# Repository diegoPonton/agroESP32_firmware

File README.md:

<h1 align="center">AgroESP32</h1>

<p align="center">
  <b>Red de sensores agrícolas de largo alcance:</b> nodos LoRa 915 MHz sobre una PCB de diseño propio,<br>
  un gateway WiFi y una plataforma web en la nube para monitorear y actuar sobre un cultivo a distancia.
</p>

<p align="center">

</p>

<p align="center">
  
  <br>
  <sub>Prototipo armado: PCB propia con el XIAO ESP32-S3 y el RFM95W, antena de 915 MHz y carcasa impresa en 3D</sub>
</p>

> **Hardware diseñado por mí.** La PCB del nodo (esquemático, ruteo, Gerbers y BOM) la diseñé en KiCad 10: un carrier de 75 × 51 mm para el Seeed XIAO ESP32-S3 y un módulo LoRa RFM95W, con borneras para conectar sensores y actuadores en campo sin soldar. Los archivos fuente están en [`hardware/`](hardware/).

---

## Contenido

- [El problema](#el-problema)
- [Resultados](#resultados)
- [Arquitectura](#arquitectura)
- [Hardware](#hardware)
  - [PCB del nodo XIAO (diseño propio)](#pcb-del-nodo-xiao-diseño-propio)
  - [Esquemático y mapa de conexiones](#esquemático-y-mapa-de-conexiones)
  - [BOM](#bom)
  - [Del diseño al nodo en campo](#del-diseño-al-nodo-en-campo)
  - [Nodo ESP32 DOIT y gateway](#nodo-esp32-doit-y-gateway)
- [Firmware](#firmware)
- [Plataforma web](#plataforma-web)
- [Pruebas de alcance](#pruebas-de-alcance)
- [Problemas de ingeniería resueltos](#problemas-de-ingeniería-resueltos)
- [Qué demuestra este proyecto](#qué-demuestra-este-proyecto)
- [Estructura del repositorio](#estructura-del-repositorio)
- [Compilar y flashear](#compilar-y-flashear)
- [Próximos pasos](#próximos-pasos)

---

## El problema

Monitorear un cultivo normalmente obliga a ir hasta el terreno. Las zonas rurales suelen no tener WiFi, cobertura celular ni tomas de corriente cerca, y las soluciones IoT comerciales son caras y dependen de suscripciones.

AgroESP32 resuelve eso con radio **LoRa a 915 MHz** (banda ISM, sin licencia): nodos de bajo consumo miden el ambiente en el cultivo y transmiten a un gateway que sí tiene internet. Desde un panel web se ven los datos en tiempo real y se mandan órdenes de vuelta a los nodos, incluida la activación de una **bomba de agua** a través de un relé de estado sólido.

## Resultados

| | |
|---|---|
| **594,66 m** | enlace más largo con recepción confirmada, sin línea de vista (edificios densos y bosque) |
| **−38 a −100 dBm** | rango de RSSI registrado en la plataforma |
| **500 lecturas** | recibidas en prueba continua con intervalo de 1 min |
| **3 tipos de nodo** | emisor XIAO (PCB propia), emisor ESP32 DOIT multi-sensor y gateway |
| **75 × 51 mm** | PCB de 2 capas, solo componentes THT, sin vías |
| **Lazo cerrado** | la plataforma no solo lee: enciende y apaga una bomba vía `set_relay` |

## Arquitectura

```mermaid
flowchart LR
    subgraph Campo["En el cultivo"]
        XIAO["Nodo XIAO ESP32-S3<br/>PCB propia<br/>BME280 + relé SSR"]
        DOIT["Nodo ESP32 DOIT<br/>SHTC3 · DS18B20 · GPS · batería"]
        Bomba["Bomba de agua"]
        XIAO -->|SSR en D0| Bomba
    end

    GW["Gateway ESP32 DOIT<br/>RFM95W + WiFi"]

    subgraph Nube["Railway"]
        API["Django REST<br/>+ Channels"]
        PG[("PostgreSQL")]
        RD[("Redis")]
        WEB["Next.js<br/>panel en tiempo real"]
    end

    XIAO <-->|LoRa 915 MHz| GW
    DOIT <-->|LoRa 915 MHz| GW
    GW -->|"HTTPS: POST telemetría<br/>GET relay de comandos"| API
    API --> PG
    API --> RD
    API <-->|REST + WebSocket| WEB
```

La telemetría sube como JSON por LoRa. El gateway le agrega el RSSI real del paquete y la publica en la API. Los comandos hacen el camino inverso: el gateway consulta si hay órdenes pendientes para ese nodo y las retransmite durante una ventana de escucha que el nodo abre después de cada transmisión. El gateway no necesita saber qué hardware tiene cada nodo; enruta todo por `device_id`.

<details>
<summary><b>Diagramas del documento de diseño</b></summary>
<br>

**Diagrama de contexto**

**Diagrama de bloques**

Ambos corresponden a la fase de diseño, con el nodo ESP32 DOIT como emisor de referencia. El documento completo está en [`docs/DISENO.md`](docs/DISENO.md).

</details>

---

## Hardware

### PCB del nodo XIAO (diseño propio)

<table>
  <tr>
    <td width="50%"></td>
    <td width="50%"></td>
  </tr>
  <tr>
    <td align="center"><sub>Layout en KiCad: F.Cu (rojo) y B.Cu (azul), plano de GND en ambas caras</sub></td>
    <td align="center"><sub>Vista 3D superior con los módulos montados</sub></td>
  </tr>
  <tr>
    <td width="50%"></td>
    <td width="50%"></td>
  </tr>
  <tr>
    <td align="center"><sub>Render isométrico</sub></td>
    <td align="center"><sub>Cara inferior (B.Cu)</sub></td>
  </tr>
</table>

**Especificaciones**

| Parámetro | Valor |
|---|---|
| Herramienta | KiCad 10 (esquemático + PCB + render 3D) |
| Dimensiones | 75 × 51 mm |
| Capas | 2 (F.Cu / B.Cu), FR-4 de 1,6 mm |
| Ancho de pista | 0,2 mm en todas las señales |
| Planos de cobre | GND en ambas caras |
| Vías | 0: todo el ruteo se resolvió en dos capas sin vías |
| Montaje | 100 % THT, soldable a mano sin equipo de SMD |
| Fijación | 4 agujeros de montaje en las esquinas |
| Conectores de campo | borneras de tornillo de 5,00 mm (MaiXu MX126) |

**Decisiones de diseño**

- **Módulos enchufables en vez de chips sueltos.** El XIAO ESP32-S3 y el breakout del RFM95W van montados como módulos. Si uno falla en campo se reemplaza sin desoldar, y la placa queda simple de fabricar y ensamblar.
- **Un puerto por bus.** Cada bornera expone una interfaz completa con su propio 3,3 V y GND, así cualquier sensor se conecta con un destornillador:
  - **J1:** entrada de alimentación (3,3 V / GND)
  - **J2:** I2C (3,3 V, GND, SDA, SCL), hoy el BME280
  - **J3:** UART (3,3 V, GND, TX, RX), reservado para un GPS
  - **J4:** GPIO/ADC (3,3 V, GND, D0), hoy maneja el relé SSR; como D0 es el único pin libre con ADC, también sirve para medir batería
- **SPI por hardware.** El RFM95W usa los pines SPI nativos del XIAO (D8, D9, D10), y CS, RST y DIO0 van a GPIO de propósito general.
- **Radio siempre habilitada.** El pin `EN` del breakout está atado a 3,3 V, y el pin de 5 V del XIAO queda sin conectar a propósito para que toda la placa trabaje en un único riel de 3,3 V.
- **Pistas cortas al módulo de radio.** El RFM95W queda al lado del XIAO para acortar las líneas SPI, con planos de GND como referencia de retorno.

### Esquemático y mapa de conexiones

También en PDF: [`hardware/esquematico.pdf`](hardware/esquematico.pdf).

Mapa de conexiones, extraído de la netlist del esquemático:

| Pin XIAO | GPIO | Red | Destino |
|---|---|---|---|
| D0 | GPIO1 | `adc` | J4-3 (GPIO/ADC → relé SSR) |
| D1 | GPIO2 | `LORA_DIO0` | U2 G0 |
| D2 | GPIO3 | `LORA_RST` | U2 RST |
| D3 | GPIO4 | `LORA_CS` | U2 CS |
| D4 | GPIO5 | `sda` | J2-3 |
| D5 | GPIO6 | `scl` | J2-4 |
| D6 | GPIO43 | `TX` | J3-3 |
| D7 | GPIO44 | `RX` | J3-4 |
| D8 | GPIO7 | `LORA_SCK` | U2 SCK |
| D9 | GPIO8 | `LORA_MISO` | U2 MISO |
| D10 | GPIO9 | `LORA_MOSI` | U2 MOSI |
| 3V3 | — | `+3.3V` | J1–J4 pin 1, U2 VIN, U2 EN |
| GND | — | `GND` | J1–J4 pin 2, U2 GND |
| 5V | — | sin conectar | — |

> En la PCB, `DIO0` y `RST` del RFM95W quedaron en D1 y D2 respectivamente, al revés que en el primer prototipo en protoboard (RST en D1, DIO0 en D2). Hay que tenerlo en cuenta al configurar `LORA_RST_PIN` y `LORA_DIO0_PIN` en `src/emisor_xiao/board_config.h`.

### BOM

**Componentes de la PCB** (exportado de KiCad: [`hardware/BOM.csv`](hardware/BOM.csv))

| Ref | Cant. | Componente | Función | Huella |
|---|---|---|---|---|
| U1 | 1 | Seeed Studio XIAO ESP32-S3 Plus | MCU: ESP32-S3, WiFi + BLE, USB-C, carga de LiPo integrada | `XIAO_ESP32_S3:MODULE_XIAO_ESP32_S3` |
| U2 | 1 | Adafruit RFM95W LoRa breakout, 915 MHz | Transceptor LoRa (SX1276) por SPI | `3073:MODULE_3073` |
| J1 | 1 | Bornera 2 pines, paso 5,00 mm (MaiXu MX126-5.0-02P) | Entrada de alimentación 3,3 V | `TerminalBlock_MaiXu_MX126-5.0-02P_1x02_P5.00mm` |
| J2, J3 | 2 | Bornera 4 pines, paso 5,00 mm (MaiXu MX126-5.0-04P) | Puertos I2C y UART | `TerminalBlock_MaiXu_MX126-5.0-04P_1x04_P5.00mm` |
| J4 | 1 | Bornera 3 pines, paso 5,00 mm (MaiXu MX126-5.0-03P) | Puerto GPIO/ADC | `TerminalBlock_MaiXu_MX126-5.0-03P_1x03_P5.00mm` |
| — | 1 | PCB 75 × 51 mm, 2 capas, FR-4 1,6 mm | Placa base | [`hardware/fabricacion/`](hardware/fabricacion/) |

> La huella de U2 es la de Adafruit 3073 (RFM96W, 433 MHz), que comparte contorno y pinout con la versión de 915 MHz (Adafruit 3072). En la placa va montada la de **915 MHz**.

**Componentes externos del nodo** (conectados por bornera o al XIAO)

| Componente | Cant. | Conexión | Función |
|---|---|---|---|
| BME280 breakout (I2C, 0x76/0x77) | 1 | J2 | Temperatura, humedad y presión atmosférica |
| Módulo relé de estado sólido (SSR) | 1 | J4 (D0) | Encendido de la bomba de agua |
| Bomba de agua | 1 | Salida del SSR | Actuador de riego |
| Antena 915 MHz con conector SMA (DIYmall) | 1 | Breakout RFM95W | Enlace LoRa |
| Antena 2,4 GHz u.FL (incluida con el XIAO) | 1 | XIAO ESP32-S3 | WiFi / BLE |
| Batería LiPo 3,7 V, 1 celda | 1 | Conector `BAT` del XIAO | Alimentación autónoma, se carga por USB-C |
| Carcasa impresa en 3D | 1 | — | Encapsulado del nodo para campo |

### Del diseño al nodo en campo

El proceso: selección de componentes, diseño de la placa en KiCad, montaje y cableado del circuito, y encapsulado de los nodos para llevarlos al campo.

### Nodo ESP32 DOIT y gateway

Además del nodo XIAO, el sistema tiene dos equipos sobre **ESP32 DOIT DevKit V1**:

**Nodo emisor multi-sensor**

| Señal | GPIO |
|---|---|
| RFM95W: CS / RST / DIO0 | 25 / 14 / 26 |
| RFM95W: SCK / MISO / MOSI | 18 / 19 / 23 |
| SHTC3 (I2C): SDA / SCL | 21 / 22 |
| DS18B20 (OneWire, pull-up 4,7 kΩ) | 4 |
| GPS (UART): RX / TX | 16 / 17 |
| Batería (ADC, divisor 1:1) | 34 |

**Gateway receptor:** mismo módulo RFM95W y mismos pines de radio, en recepción continua por interrupción. Usa el WiFi del ESP32 para publicar en la nube y transmite a 13 dBm (los emisores, a 20 dBm).

**Perfil de radio común**

| Parámetro | Valor |
|---|---|
| Frecuencia | 915,0 MHz (ISM) |
| Spreading factor / ancho de banda | SF7 / 125 kHz |
| Coding rate | 4/5 |
| Sync word | `0x12` (red privada) |
| Payload máximo | 250 bytes |

---

## Firmware

Un solo proyecto **PlatformIO** (C++ / Arduino) con un entorno por equipo:

| Entorno | Placa | Rol |
|---|---|---|
| `emisor` | ESP32 DOIT DevKit V1 | Nodo multi-sensor: SHTC3, DS18B20, GPS, batería |
| `emisor_xiao` | Seeed XIAO ESP32-S3 | Nodo de la PCB: BME280 + relé SSR |
| `receptor` | ESP32 DOIT DevKit V1 | Gateway LoRa → WiFi → API |

**Características**

- **RadioLib** sobre el SX1276. TX y RX bloqueantes leyendo el pin de IRQ, sin acceso SPI dentro de interrupciones (ver [problemas resueltos](#problemas-de-ingeniería-resueltos)).
- **Configuración en tres niveles:** NVS (`Preferences`) → `secrets.h` generado por la plataforma → modo *provisioning* que espera un JSON por serial. Las credenciales nunca se versionan.
- **Payload JSON adaptativo:** si el paquete supera 250 bytes, el nodo DOIT recorta el bloque GPS por niveles (todo → sin altitud/velocidad/HDOP → solo lat/lon → sin GPS).
- **Comandos remotos** recibidos en una ventana de escucha de 7 s después de cada TX y persistidos en NVS:

| Comando | Parámetros | Efecto |
|---|---|---|
| `set_sleep` | `{"minutes": N}` | Cambia el intervalo de envío (1–1440 min) |
| `enable_sensor` | `{"sensor": "...", "enable": bool}` | Activa o desactiva un sensor (nodo DOIT) |
| `set_relay` | `{"state": bool}` | Enciende o apaga el relé SSR (nodo XIAO); el estado sobrevive a reinicios |
| `set_device_id` | `{"device_id": "..."}` | Reasigna el ID y reinicia |
| `restart` | `{}` | Reinicio por software |

**Ejemplo de payload del nodo XIAO**

```json
{
  "device_id": "e2",
  "amb": { "ok": true, "temp_c": 24.8, "hum_pct": 52.3, "pressure_hpa": 1013.2 },
  "relay": { "on": false },
  "rssi": -38
}
```

`rssi` lo agrega el gateway con la medición real del paquete recibido.

**Ciclo de vida del nodo (diseño)**

El diseño contempla *deep sleep* entre ciclos con caché del GPS en memoria RTC (arranque en caliente ≤ 30 s contra 60 s en frío). Los builds de prueba transmiten cada ~10 s para iterar rápido sobre el enlace.

---

## Plataforma web

Código en el repositorio [**AgroPlatfrom**](https://github.com/diegoPonton/AgroPlatfrom), desplegado en Railway con auto-deploy desde `main`.

| Capa | Tecnología |
|---|---|
| Backend | Django 5, Django REST Framework, Django Channels (WebSocket) |
| Datos | PostgreSQL, Redis como channel layer |
| Frontend | Next.js (App Router), TanStack Query, Recharts, Leaflet, shadcn/ui |
| Infraestructura | Railway: 4 servicios, migraciones automáticas en cada deploy |

**Funcionalidades**

- Autenticación JWT y organizaciones multi-usuario.
- Registro de nodos y asignación de cada emisor a su gateway.
- Ingesta de telemetría autenticada con el token del gateway; cada lectura guarda qué gateway la recibió.
- Panel en tiempo real por WebSocket: KPIs, historial graficado, RSSI y mapa GPS.
- Cola de comandos con estados (`pending` → `relayed` → `acked`) retransmitidos por el gateway.
- Generación de `secrets.h` por dispositivo y **flasheo de firmware desde el navegador** (Web Serial + esptool-js).

---

## Pruebas de alcance

El enlace se probó en un campus universitario con edificios densos, arbolado y un lago, **sin línea de vista despejada** en ninguno de los tres trayectos:

| Prueba | Trayecto | Distancia | Resultado |
|---|---|---|---|
| 1 | Entre bloques de aulas | 295,00 m | Recepción confirmada |
| 2 | Sobre bosque y lago | **594,66 m** | Recepción confirmada (enlace más largo) |
| 3 | Patio y arbolado interior | 201,57 m | Recepción confirmada |

Durante las pruebas la plataforma registró 500 lecturas con intervalo de 1 minuto y RSSI entre −38 y −100 dBm. Con línea de vista, LoRa a SF7 alcanza bastante más; estas cifras son el peor caso urbano.

---

## Problemas de ingeniería resueltos

Una parte importante del proyecto fue depurar hardware real:

- **Sensor mal identificado.** Una placa vendida como "GY-39" se trató primero como BME280 y nunca respondió. Al revisar el hardware resultó ser un módulo 4 en 1 con un **SPL06-007** para presión, cuyos registros no coinciden con los del BME280. La solución fue leer directamente el **SHTC3** que la misma placa expone en I2C (`0x70`), y usar un BME280 genuino en el nodo XIAO.
- **TX colgado con RadioHead.** Después de esperar ~60 s el fix del GPS, el SX1276 no volvía a STANDBY y cada transmisión daba timeout (`IRQ_FLAGS = 0x00`, nunca `TxDone`). Además, acceder a SPI dentro de la ISR de DIO0 provocaba reinicios. Migrar a **RadioLib** con TX/RX bloqueantes por sondeo del pin IRQ eliminó ambos problemas.
- **Pines intercambiados entre prototipo y PCB.** En la placa propia, RST y DIO0 del RFM95W quedaron en pines distintos a los del prototipo en protoboard, así que la asignación de pines del prototipo no servía para la placa. Se corrigió reasignando los pines en el firmware, sin rehacer la PCB.
- **404 en la ingesta.** Al sumar un nodo nuevo, la API devolvía 404. No era un bug: el backend solo acepta telemetría de dispositivos registrados en la misma organización que el gateway, una restricción de seguridad multi-tenant intencional.

## Qué demuestra este proyecto

| Área | Habilidades |
|---|---|
| **Diseño de hardware** | Captura de esquemático, ruteo de PCB de 2 capas, planos de GND, generación de Gerbers y BOM en KiCad; selección de componentes; montaje y depuración con multímetro |
| **Sistemas embebidos** | ESP32 / ESP32-S3, buses SPI, I2C, UART, OneWire y ADC; NVS; manejo de interrupciones; gestión de energía |
| **Radiofrecuencia** | Configuración de LoRa (SF, BW, CR, sync word), pruebas de alcance en campo, análisis de RSSI |
| **Firmware** | C++ / Arduino con PlatformIO, protocolo propio sobre LoRa, comandos remotos con persistencia, aprovisionamiento seguro de credenciales |
| **Backend y cloud** | Django REST, WebSocket con Channels, PostgreSQL, Redis, despliegue continuo en Railway |
| **Frontend** | Next.js, visualización en tiempo real, Web Serial API para flashear dispositivos desde el navegador |

---

## Estructura del repositorio

```
agroESP32_firmware/
├── hardware/
│   ├── kicad/                  # Proyecto KiCad 10 (esquemático + PCB)
│   ├── fabricacion/            # Gerbers + taladros listos para enviar a fabricar
│   ├── BOM.csv                 # Lista de materiales exportada de KiCad
│   └── esquematico.pdf
├── src/
│   ├── emisor/                 # Nodo ESP32 DOIT multi-sensor
│   ├── emisor_xiao/            # Nodo XIAO ESP32-S3 (PCB propia)
│   └── receptor/               # Gateway LoRa → WiFi
├── docs/
│   ├── DISENO.md               # Documento de diseño (alcance, diagramas, plan de pruebas, referencias)
│   ├── RESUMEN_TECNICO.md      # Estado técnico detallado y bitácora de decisiones
│   └── images/
└── platformio.ini
```

Los modelos 3D STEP del XIAO y del breakout de Adafruit son de terceros y no se incluyen. Para el render 3D en KiCad, descargalos de Seeed Studio y Adafruit y colocalos en `hardware/kicad/3dModels/`.

## Compilar y flashear

Requiere [PlatformIO](https://platformio.org/).

```bash
git clone https://github.com/diegoPonton/agroESP32_firmware.git
cd agroESP32_firmware

# Cada equipo necesita su secrets.h (no versionado)
cp src/emisor_xiao/secrets.h.example src/emisor_xiao/secrets.h

pio run -e emisor_xiao -t upload --upload-port COMx
pio device monitor -e emisor_xiao -p COMx
```

Lo mismo aplica para `emisor` y `receptor`. Sin `secrets.h`, el equipo arranca en modo provisioning y espera su configuración por serial.

Para fabricar la placa, subí [`hardware/fabricacion/agroESP32_PCB_gerbers.zip`](hardware/fabricacion/agroESP32_PCB_gerbers.zip) a cualquier fabricante de PCB (2 capas, 1,6 mm).

## Próximos pasos

- **Riego automático:** usar las lecturas de temperatura y humedad (déficit de presión de vapor) para decidir cuándo encender la bomba con `set_relay`, cerrando el lazo sin intervención humana.
- *Deep sleep* en los builds de campo para llevar la autonomía a meses.
- Cifrado AES del enlace LoRa.
- Medición de batería en el nodo XIAO por D0 (ADC) con divisor resistivo.
- Carcasa sellada para intemperie.
- Flasheo del nodo XIAO desde la plataforma web.

---

## Autor

**Diego Pontón Vaca**: diseño de PCB, firmware y plataforma web.

Documentación completa del diseño: [`docs/DISENO.md`](docs/DISENO.md) · Estado técnico detallado: [`docs/RESUMEN_TECNICO.md`](docs/RESUMEN_TECNICO.md)

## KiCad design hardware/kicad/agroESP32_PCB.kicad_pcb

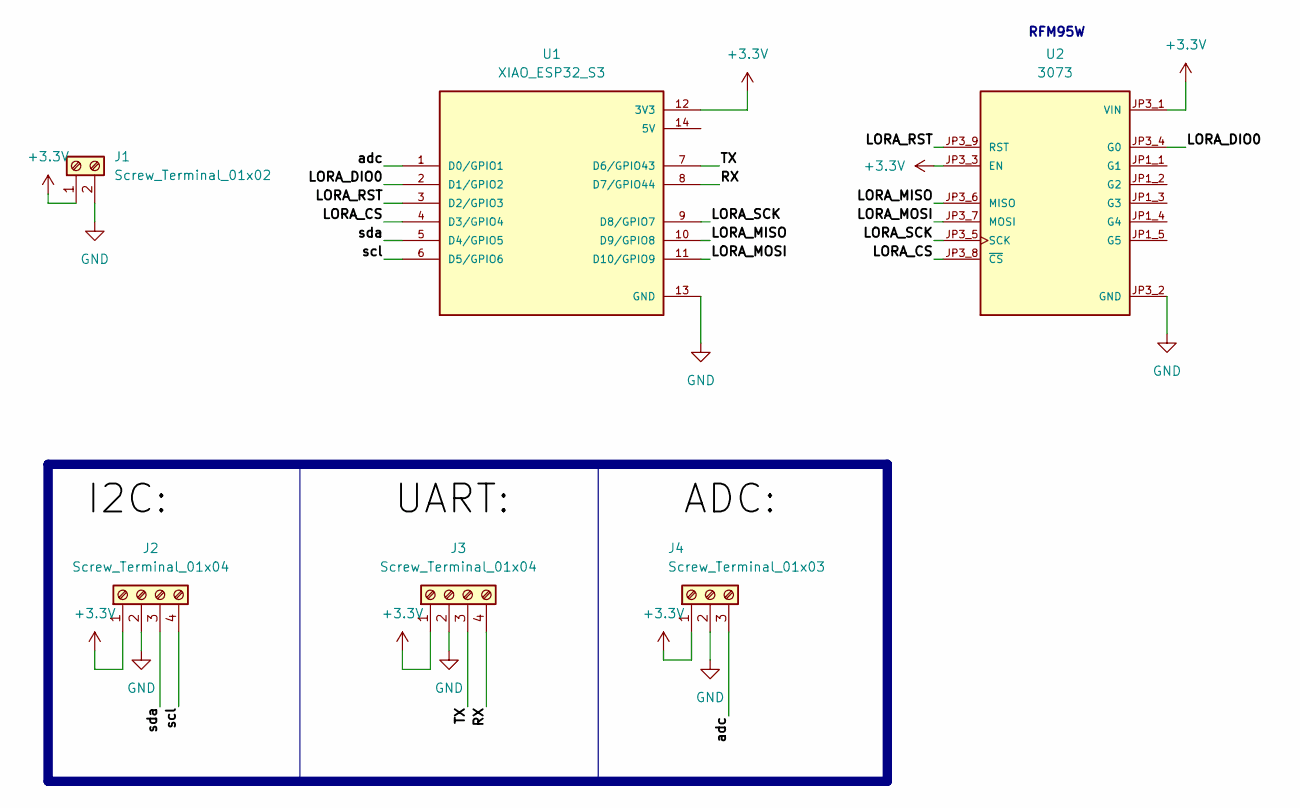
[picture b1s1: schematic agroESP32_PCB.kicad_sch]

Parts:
J1: Screw_Terminal_01x02; TerminalBlock_MaiXu_MX126-5.0-02P_1x02_P5.00mm
J2, J3: Screw_Terminal_01x04; TerminalBlock_MaiXu_MX126-5.0-04P_1x04_P5.00mm
J4: Screw_Terminal_01x03; TerminalBlock_MaiXu_MX126-5.0-03P_1x03_P5.00mm
U1: XIAO_ESP32_S3; MODULE_XIAO_ESP32_S3; PARTREV April 22nd, 2026
U2: 3073; MODULE_3073; PARTREV 2023-10-24

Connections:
+3.3V: J1.1, J2.1, J3.1, J4.1, U1.12 (3V3), U2.JP3_1 (VIN), U2.JP3_3 (EN)
/LORA_CS: U1.4 (D3/GPIO4), U2.JP3_8 (~CS)
/LORA_DIO0: U1.2 (D1/GPIO2), U2.JP3_4 (G0)
/LORA_MISO: U1.10 (D9/GPIO8), U2.JP3_6 (MISO)
/LORA_MOSI: U1.11 (D10/GPIO9), U2.JP3_7 (MOSI)
/LORA_RST: U1.3 (D2/GPIO3), U2.JP3_9 (RST)
/LORA_SCK: U1.9 (D8/GPIO7), U2.JP3_5 (SCK)
/RX: J3.4, U1.8 (D7/GPIO44)
/TX: J3.3, U1.7 (D6/GPIO43)
/adc: J4.3, U1.1 (D0/GPIO1)
/scl: J2.4, U1.6 (D5/GPIO6)
/sda: J2.3, U1.5 (D4/GPIO5)
GND: J1.2, J2.2, J3.2, J4.2, U1.13 (GND), U2.JP3_2 (GND)

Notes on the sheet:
RFM95W

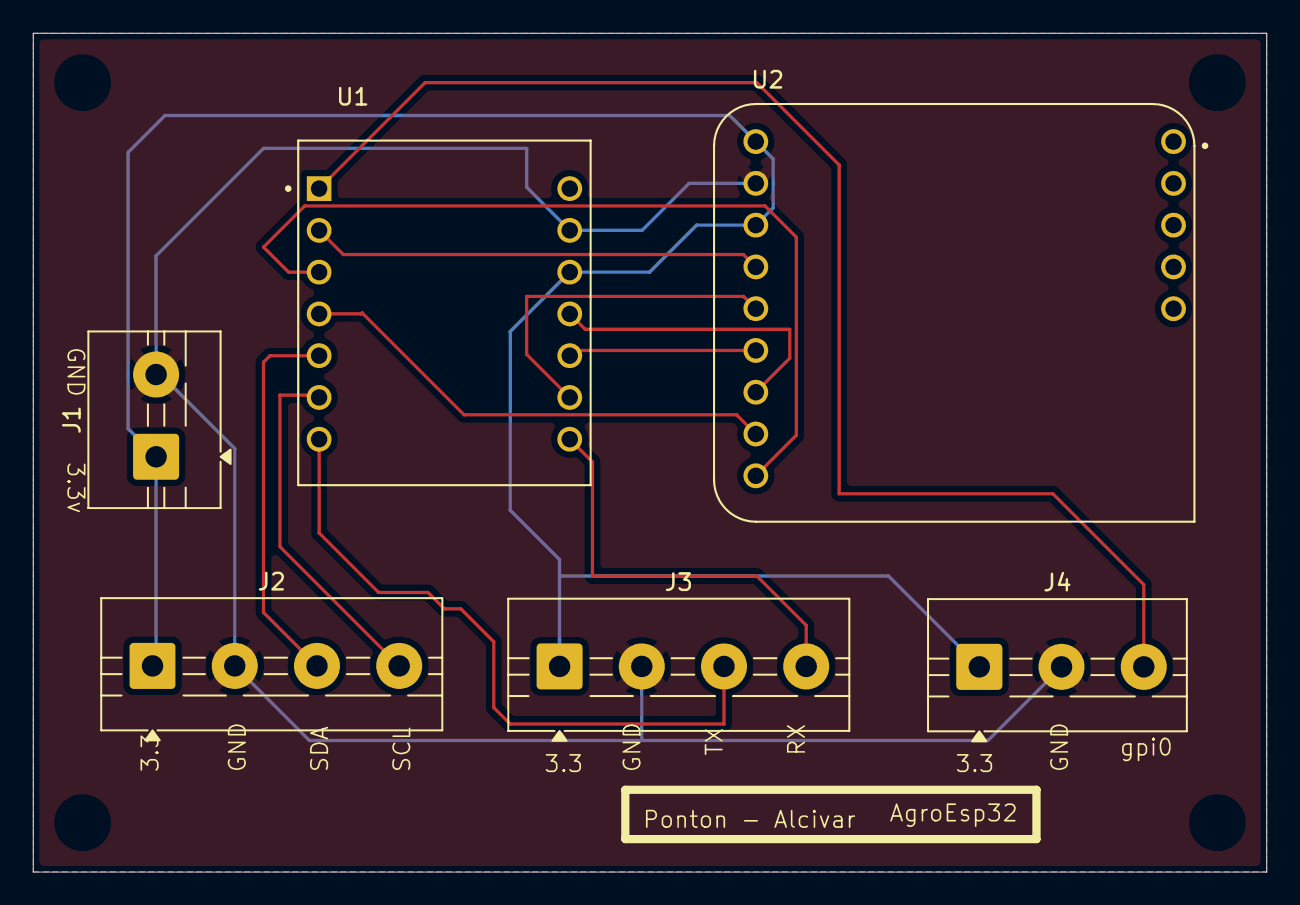
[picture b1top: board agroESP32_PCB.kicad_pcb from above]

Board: 2 copper layers, 75.0 x 51.0 mm, 6 parts (0 on the bottom side), 13 nets.

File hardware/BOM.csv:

"Reference","Value","Footprint","QUANTITY","Description","Datasheet","MPN","Manufacturer"
"J1","Screw_Terminal_01x02","TerminalBlock:TerminalBlock_MaiXu_MX126-5.0-02P_1x02_P5.00mm","1","Generic screw terminal, single row, 01x02, script generated (kicad-library-utils/schlib/autogen/connector/)","","",""
"J2,J3","Screw_Terminal_01x04","TerminalBlock:TerminalBlock_MaiXu_MX126-5.0-04P_1x04_P5.00mm","2","Generic screw terminal, single row, 01x04, script generated (kicad-library-utils/schlib/autogen/connector/)","","",""
"J4","Screw_Terminal_01x03","TerminalBlock:TerminalBlock_MaiXu_MX126-5.0-03P_1x03_P5.00mm","1","Generic screw terminal, single row, 01x03, script generated (kicad-library-utils/schlib/autogen/connector/)","","",""
"U1","XIAO_ESP32_S3","XIAO_ESP32_S3:MODULE_XIAO_ESP32_S3","1","Seeed Studio XIAO ESP32-S3 Development Board Supports Wi-Fi & Bluetooth","","","Seeed Studio"
"U2","3073","3073:MODULE_3073","1","Adafruit RFM96W LoRa Radio Transceiver Breakout - 433 MHz | Adafruit Industries 3073","","","Adafruit Industries LLC"

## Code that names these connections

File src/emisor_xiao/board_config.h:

#pragma once
// =====================================================
// Nodo emisor — Seeed XIAO ESP32-S3 + RFM95W (módulo externo por SPI)
// Único sensor: BME280 (ambiente: temp/hum/presión) por I2C.
// Mismo perfil de radio que el emisor DOIT para que el receptor
// existente lo reciba sin cambios.
// =====================================================

// --- LoRa SPI (RFM95W, 915 MHz) ---
#define LORA_CS_PIN    D3
#define LORA_RST_PIN   D1
#define LORA_DIO0_PIN  D2
#define LORA_SCK_PIN   D8
#define LORA_MISO_PIN  D9
#define LORA_MOSI_PIN  D10
#define LORA_FREQ_MHZ  915.0f
// SF: 0 = default RadioLib (SF7). Cambiar solo si el receptor usa el mismo SF.
#define LORA_SF_DEFAULT   0
#define LORA_TX_DBM       20
#define LORA_SYNC_WORD    0x12   // 0x12 = red privada, 0x34 = LoRaWAN público
#define CMD_WINDOW_MS      7000  // ventana de escucha LoRa tras cada TX (ms)

// --- I2C (BME280) ---
#define I2C_SDA_PIN    D4
#define I2C_SCL_PIN    D5
#define BME280_I2C_ADDR 0x76   // 0x76 en la mayoría de los breakouts; 0x77 en algunos

// --- Actuador: relevador de estado sólido ---
#define RELAY_PIN        D0
#define RELAY_ACTIVE_HIGH  true   // false si el módulo SSR activa en LOW

// --- Comportamiento ---
#define DEFAULT_SLEEP_MIN  10
